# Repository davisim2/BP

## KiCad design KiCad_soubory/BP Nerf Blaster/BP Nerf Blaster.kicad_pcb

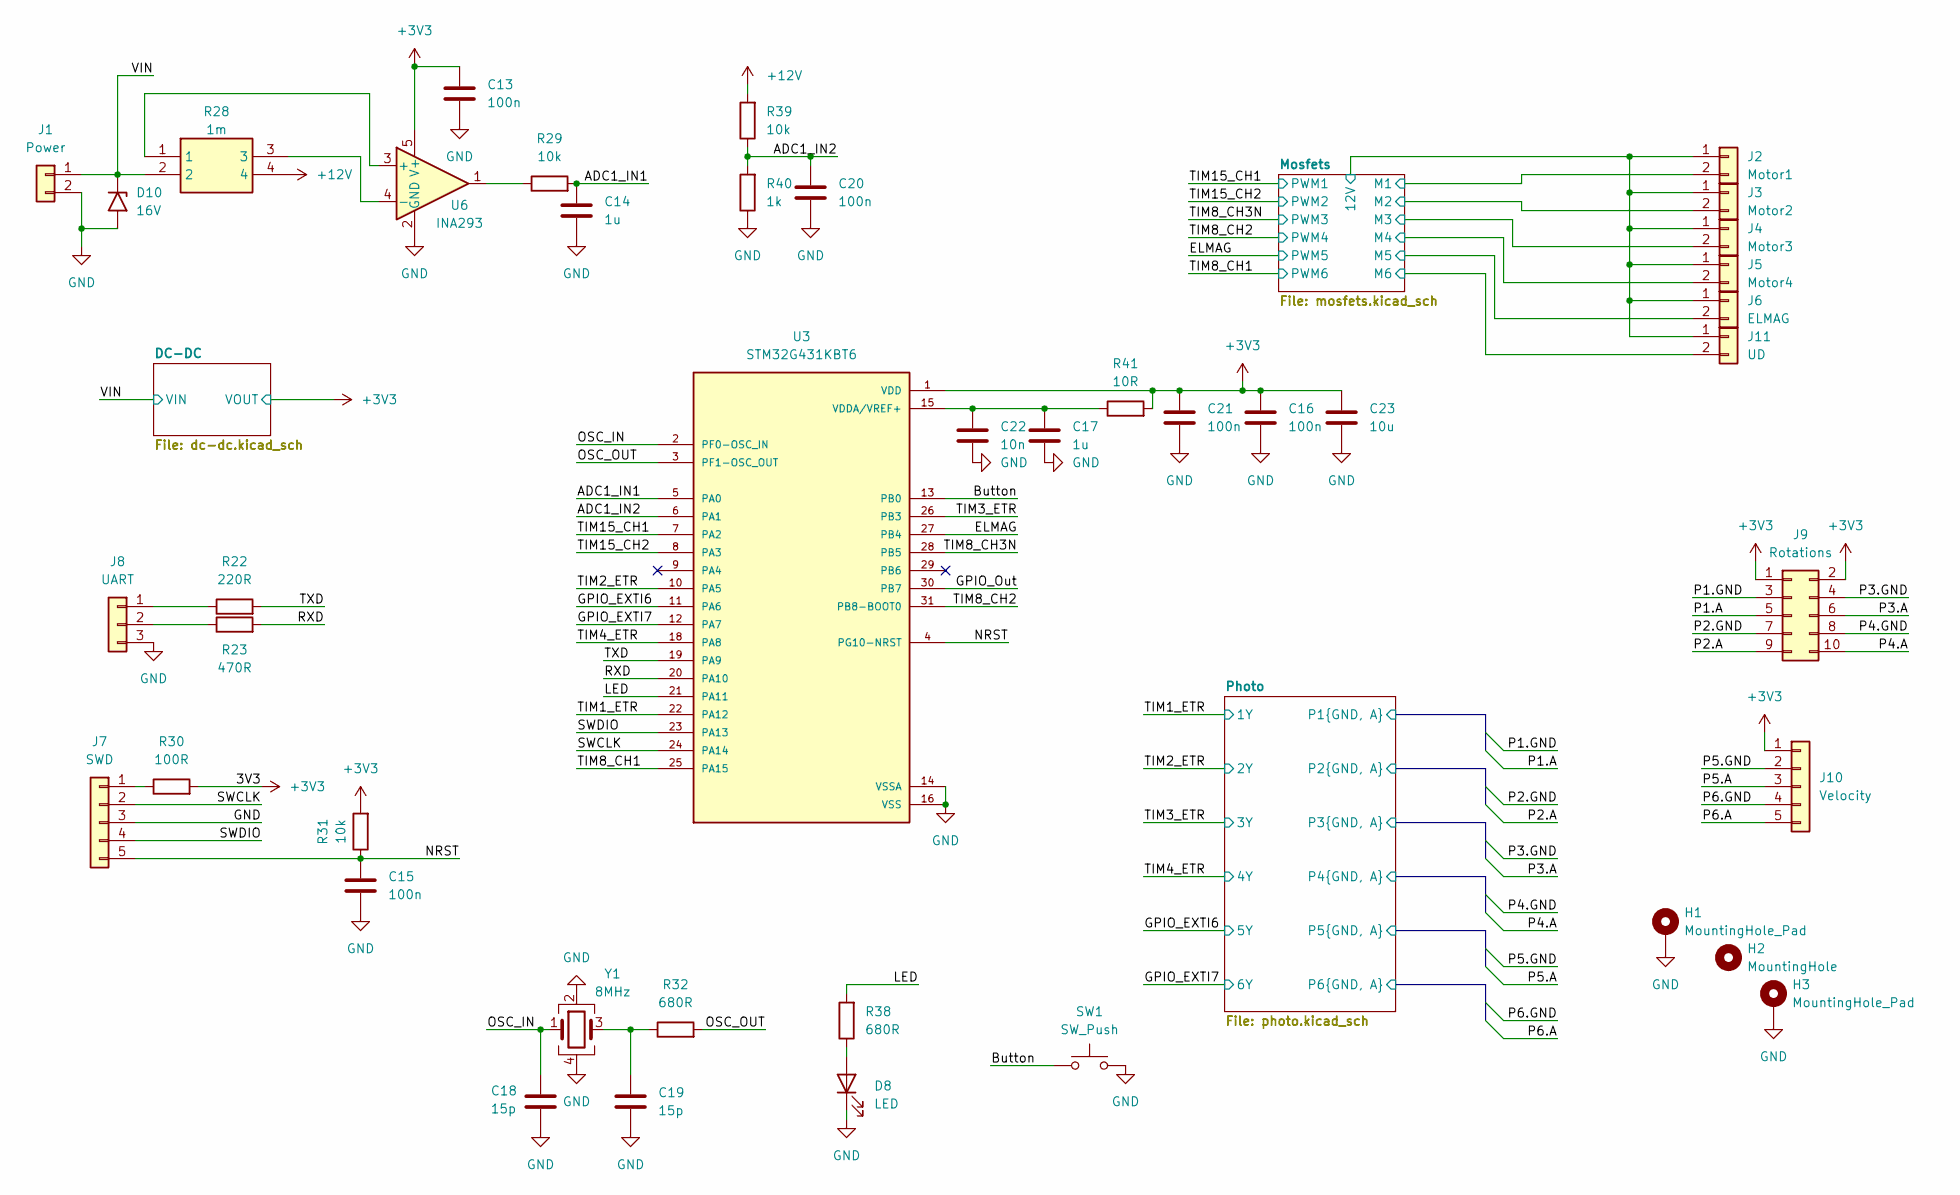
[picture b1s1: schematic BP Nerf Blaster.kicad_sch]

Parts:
C13, C15, C16, C20, C21: 100n; C_0805_2012Metric
C14, C17: 1u; C_0805_2012Metric
C18, C19: 15p; C_0805_2012Metric
C22: 10n; C_0603_1608Metric_Pad1.08x0.95mm_HandSolder
C23: 10u; C_0805_2012Metric
D8: LED; LED_D3.0mm
D10: 16V; D_SMB
H1, H3: MountingHole_Pad; MountingHole_3.2mm_M3_DIN965_Pad
H2: MountingHole; Hole
J1: Power; XT30-f
J2: Motor1; XT30-f
J3: Motor2; XT30-f
J4: Motor3; XT30-f
J5: Motor4; XT30-f
J6: ELMAG; XT30-f
J7: SWD; PinHeader_1x05_P1.27mm_Vertical
J8: UART; PinHeader_1x03_P2.54mm_Vertical
J9: Rotations; PinHeader_2x05_P2.54mm_Vertical
J10: Velocity; PinHeader_1x05_P2.54mm_Vertical
J11: UD; XT30-f
R22: 220R; R_0805_2012Metric
R23: 470R; R_0805_2012Metric
R28: 1m; WSK25121L000FEA; Mouser Part Number 71-WSK25121L000FEA
R29, R31, R39: 10k; R_0805_2012Metric
R30: 100R; R_0805_2012Metric
R32, R38: 680R; R_0805_2012Metric
R40: 1k; R_0805_2012Metric
R41: 10R; R_0805_2012Metric
SW1: SW_Push; SW_PUSH_6mm_H9.5mm
U3: STM32G431KBT6; QFP80P900X900X160-32N; PARTREV 2
U6: INA293; SOT-23-5
Y1: 8MHz; Crystal_SMD_SeikoEpson_FA238-4Pin_3.2x2.5mm

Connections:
+3V3: C13.1, C16.1, C21.1, C23.1, J9.1, J9.2, J10.1, R30.2, R31.2, R41.2, U3.1 (VDD), U3.17 (VDD), U6.5 (V+); also elsewhere on the board
+12V: J2.1, J3.1, J4.1, J5.1, J6.1, J11.1, R28.4, R39.2; also elsewhere on the board
/ADC1_IN1: C14.1, R29.2, U3.5 (PA0)
/ADC1_IN2: C20.1, R39.1, R40.2, U3.6 (PA1)
/Button: SW1.1, U3.13 (PB0)
/ELMAG: U3.27 (PB4); also elsewhere on the board
/GPIO_EXTI6: U3.11 (PA6); also elsewhere on the board
/GPIO_EXTI7: U3.12 (PA7); also elsewhere on the board
/GPIO_Out: U3.30 (PB7)
/LED: R38.2, U3.21 (PA11)
/Mosfets/M1: J2.2; also elsewhere on the board
/Mosfets/M2: J3.2; also elsewhere on the board
/Mosfets/M3: J4.2; also elsewhere on the board
/Mosfets/M4: J5.2; also elsewhere on the board
/Mosfets/M5: J6.2; also elsewhere on the board
/Mosfets/M6: J11.2; also elsewhere on the board
/NRST: C15.1, J7.5, R31.1, U3.4 (PG10-NRST)
/OSC_IN: C18.1, U3.2 (PF0-OSC_IN), Y1.1
/OSC_OUT: R32.2, U3.3 (PF1-OSC_OUT)
/Photo/P1.A: J9.5; also elsewhere on the board
/Photo/P1.GND: J9.3; also elsewhere on the board
/Photo/P2.A: J9.9; also elsewhere on the board
/Photo/P2.GND: J9.7; also elsewhere on the board
/Photo/P3.A: J9.6; also elsewhere on the board
/Photo/P3.GND: J9.4; also elsewhere on the board
/Photo/P4.A: J9.10; also elsewhere on the board
/Photo/P4.GND: J9.8; also elsewhere on the board
/Photo/P5.A: J10.3; also elsewhere on the board
/Photo/P5.GND: J10.2; also elsewhere on the board
/Photo/P6.A: J10.5; also elsewhere on the board
/RXD: R23.2, U3.20 (PA10)
/SWCLK: J7.2, U3.24 (PA14)
/SWDIO: J7.4, U3.23 (PA13)
/TIM1_ETR: U3.22 (PA12); also elsewhere on the board
/TIM2_ETR: U3.10 (PA5); also elsewhere on the board
/TIM3_ETR: U3.26 (PB3); also elsewhere on the board
/TIM4_ETR: U3.18 (PA8); also elsewhere on the board
/TIM8_CH1: U3.25 (PA15); also elsewhere on the board
/TIM8_CH2: U3.31 (PB8-BOOT0); also elsewhere on the board
/TIM8_CH3N: U3.28 (PB5); also elsewhere on the board
/TIM15_CH1: U3.7 (PA2); also elsewhere on the board
/TIM15_CH2: U3.8 (PA3); also elsewhere on the board
/TXD: R22.2, U3.19 (PA9)
/VIN: D10.1 (A1), J1.1, R28.2; also elsewhere on the board
unnamed: C19.1, R32.1, Y1.3
unnamed: D8.2 (A), R38.1
unnamed: J7.1, R30.1
unnamed: J8.1, R22.1
unnamed: J8.2, R23.1
unnamed: R29.1, U6.1
unnamed: C17.1, C22.1, R41.1, U3.15 (VDDA/VREF+)
unnamed: R28.1, U6.3 (+)
unnamed: R28.3, U6.4 (-)

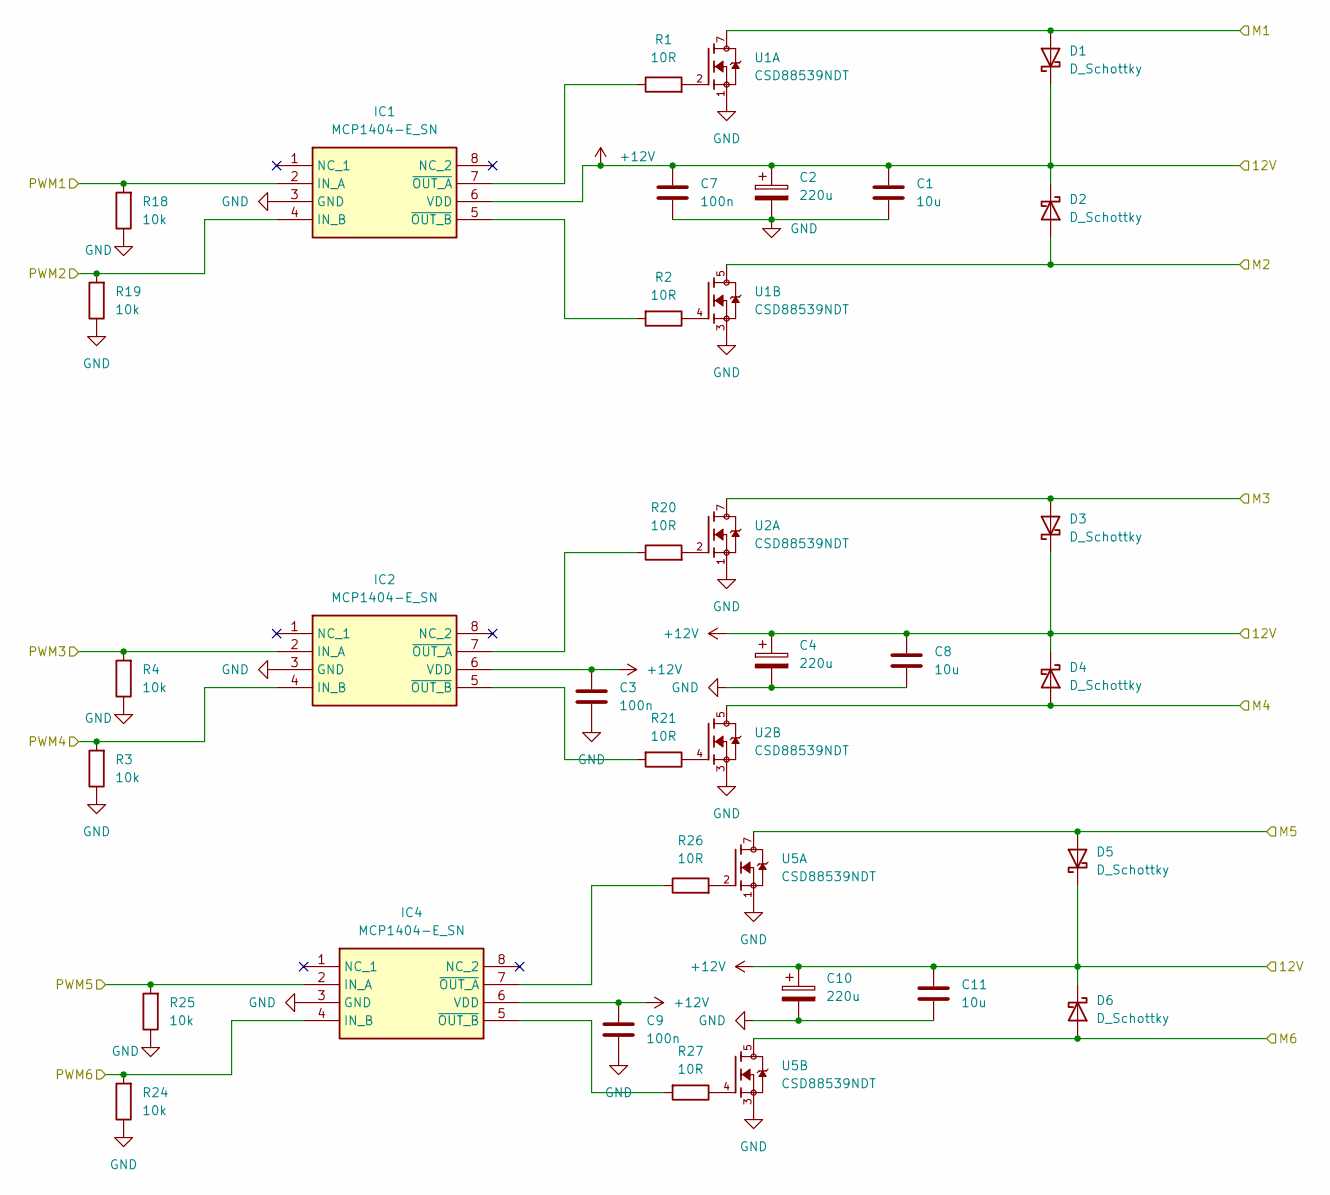
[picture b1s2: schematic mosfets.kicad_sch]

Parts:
C1, C8, C11: 10u; C_1206_3216Metric
C2, C4: 220u; C_Elec_8x10.2
C3, C7, C9: 100n; C_0805_2012Metric
C10: 220u; C_Elec_8x10.2; Mouser 80-EEV227M025A9MAA
D1: D_Schottky; D_SMA; Mouser 625-SSA34-E3
D2, D3, D4, D5, D6: D_Schottky; D_SMA
IC1, IC2, IC4: MCP1404-E_SN; SOIC127P600X175-8N; Mouser Part Number 579-MCP1404-E/SN
R1, R2, R20, R21, R26, R27: 10R; R_0805_2012Metric
R3, R4, R18, R19, R24, R25: 10k; R_0805_2012Metric
U1, U2, U5: CSD88539NDT; SOIC127P600X175-8N; PARTREV February 2014

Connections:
+12V: C1.1, C2.1, C3.1, C4.1, C7.1, C8.1, C9.1, C10.1, C11.1, D1.1 (K), D2.1 (K), D3.1 (K), D4.1 (K), D5.1 (K), D6.1 (K), IC1.6 (VDD), IC2.6 (VDD), IC4.6 (VDD); also elsewhere on the board
/ELMAG: IC4.2 (IN_A), R25.2; also elsewhere on the board
/Mosfets/M1: D1.2 (A), U1.7, U1.8; also elsewhere on the board
/Mosfets/M2: D2.2 (A), U1.5, U1.6; also elsewhere on the board
/Mosfets/M3: D3.2 (A), U2.7, U2.8; also elsewhere on the board
/Mosfets/M4: D4.2 (A), U2.5, U2.6; also elsewhere on the board
/Mosfets/M5: D5.2 (A), U5.7, U5.8; also elsewhere on the board
/Mosfets/M6: D6.2 (A), U5.5, U5.6; also elsewhere on the board
/TIM8_CH1: IC4.4 (IN_B), R24.2; also elsewhere on the board
/TIM8_CH2: IC2.4 (IN_B), R3.2; also elsewhere on the board
/TIM8_CH3N: IC2.2 (IN_A), R4.2; also elsewhere on the board
/TIM15_CH1: IC1.2 (IN_A), R18.2; also elsewhere on the board
/TIM15_CH2: IC1.4 (IN_B), R19.2; also elsewhere on the board
unnamed: IC1.7 (~OUT_A), R1.1
unnamed: IC1.5 (~OUT_B), R2.2
unnamed: IC2.7 (~OUT_A), R20.1
unnamed: IC2.5 (~OUT_B), R21.2
unnamed: IC4.7 (~OUT_A), R26.1
unnamed: IC4.5 (~OUT_B), R27.2
unnamed: R1.2, U1.2
unnamed: R2.1, U1.4
unnamed: R20.2, U2.2
unnamed: R21.1, U2.4
unnamed: R26.2, U5.2
unnamed: R27.1, U5.4

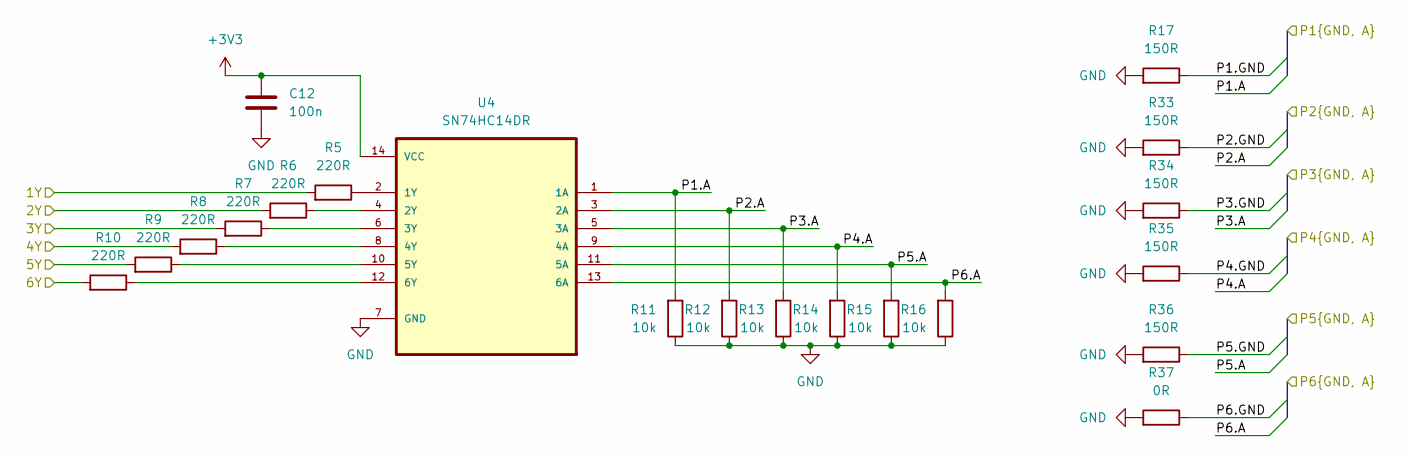
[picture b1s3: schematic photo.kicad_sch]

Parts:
C12: 100n; C_0805_2012Metric
R5, R6, R7, R8, R9, R10: 220R; R_0805_2012Metric
R11, R12, R13, R14, R15, R16: 10k; R_0805_2012Metric
R17, R33, R34, R35, R36: 150R; R_0805_2012Metric
R37: 0R; R_0805_2012Metric
U4: SN74HC14DR; SOIC127P600X175-14N

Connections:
+3V3: C12.1, U4.14 (VCC); also elsewhere on the board
/GPIO_EXTI6: R9.2; also elsewhere on the board
/GPIO_EXTI7: R10.2; also elsewhere on the board
/Photo/P1.A: R11.2, U4.1 (1A); also elsewhere on the board
/Photo/P1.GND: R17.1; also elsewhere on the board
/Photo/P2.A: R12.2, U4.3 (2A); also elsewhere on the board
/Photo/P2.GND: R33.1; also elsewhere on the board
/Photo/P3.A: R13.2, U4.5 (3A); also elsewhere on the board
/Photo/P3.GND: R34.1; also elsewhere on the board
/Photo/P4.A: R14.2, U4.9 (4A); also elsewhere on the board
/Photo/P4.GND: R35.1; also elsewhere on the board
/Photo/P5.A: R15.2, U4.11 (5A); also elsewhere on the board
/Photo/P5.GND: R36.1; also elsewhere on the board
/Photo/P6.A: R16.2, U4.13 (6A); also elsewhere on the board
/Photo/P6.GND: R37.1
/TIM1_ETR: R5.2; also elsewhere on the board
/TIM2_ETR: R6.2; also elsewhere on the board
/TIM3_ETR: R7.2; also elsewhere on the board
/TIM4_ETR: R8.2; also elsewhere on the board
unnamed: R5.1, U4.2 (1Y)
unnamed: R6.1, U4.4 (2Y)
unnamed: R7.1, U4.6 (3Y)
unnamed: R8.1, U4.8 (4Y)
unnamed: R9.1, U4.10 (5Y)
unnamed: R10.1, U4.12 (6Y)

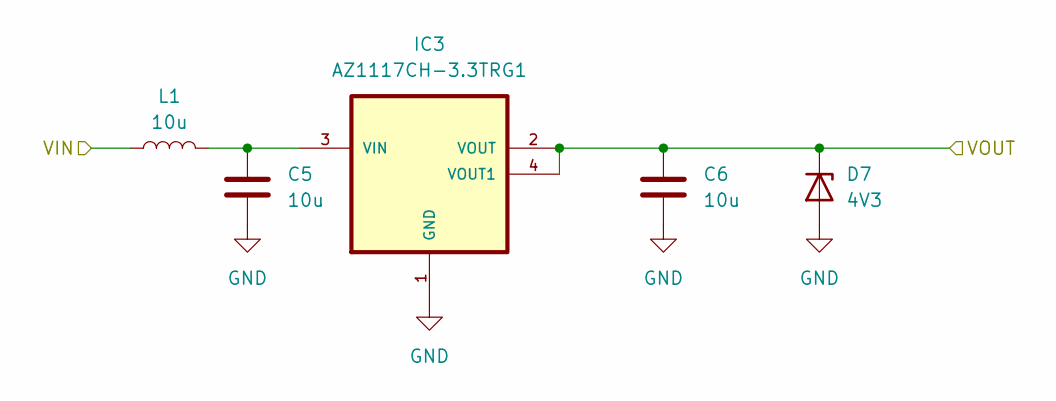
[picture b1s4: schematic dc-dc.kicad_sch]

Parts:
C5, C6: 10u; C_1206_3216Metric
D7: 4V3; D_SMA
IC3: AZ1117CH-3.3TRG1; SOT223
L1: 10u; L_0805_2012Metric

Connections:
+3V3: C6.1, D7.1 (K), IC3.2 (VOUT), IC3.4 (VOUT1); also elsewhere on the board
/VIN: L1.1; also elsewhere on the board
unnamed: C5.1, IC3.3 (VIN), L1.2

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
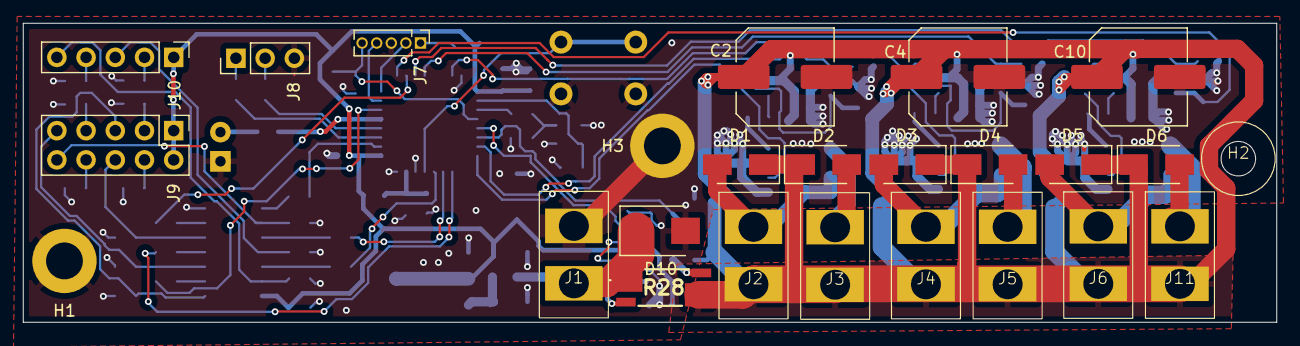
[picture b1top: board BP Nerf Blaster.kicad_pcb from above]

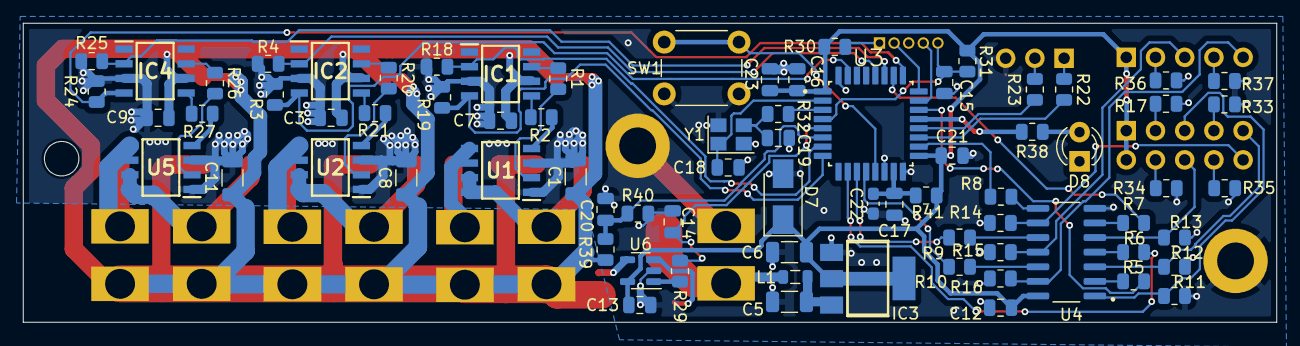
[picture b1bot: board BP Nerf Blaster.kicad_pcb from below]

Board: 2 copper layers, 109.0 x 26.0 mm, 100 parts (75 on the bottom side), 72 nets.

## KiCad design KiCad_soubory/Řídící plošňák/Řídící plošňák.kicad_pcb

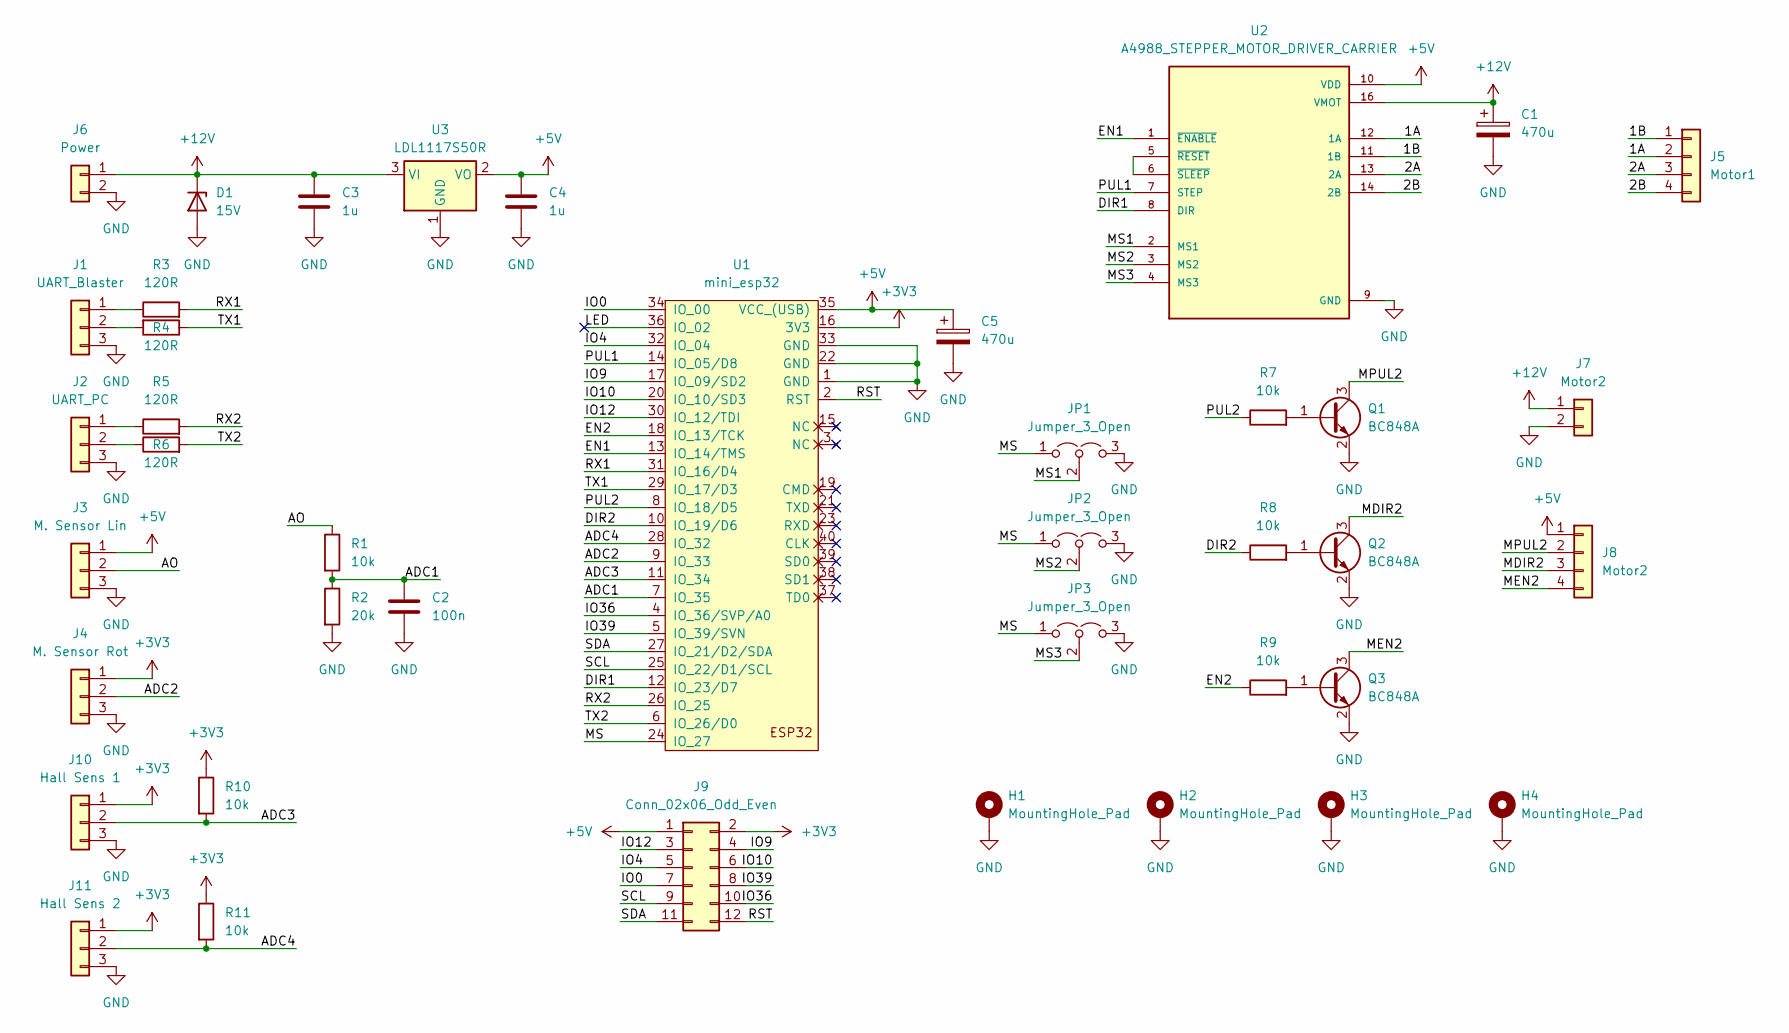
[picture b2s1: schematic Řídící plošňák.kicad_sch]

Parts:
C1, C5: 470u; CP_Elec_8x10
C2: 100n; C_1206_3216Metric_Pad1.33x1.80mm_HandSolder
C3, C4: 1u; C_1206_3216Metric_Pad1.33x1.80mm_HandSolder
D1: 15V; D_SMB_Handsoldering
H1, H2, H3, H4: MountingHole_Pad; MountingHole_4.3mm_M4_DIN965_Pad
J1: UART_Blaster; PinHeader_1x03_P2.54mm_Vertical
J2: UART_PC; PinHeader_1x03_P2.54mm_Vertical
J3: M. Sensor Lin; PinHeader_1x03_P2.54mm_Vertical
J4: M. Sensor Rot; PinHeader_1x03_P2.54mm_Vertical
J5: Motor1; TE_282822-4
J6: Power; XT30-f
J7: Motor2; XT30-f
J8: Motor2; PinHeader_1x04_P2.54mm_Vertical
J9: Conn_02x06_Odd_Even; PinHeader_2x06_P2.54mm_Vertical
J10: Hall Sens 1; PinHeader_1x03_P2.54mm_Vertical
J11: Hall Sens 2; PinHeader_1x03_P2.54mm_Vertical
JP1, JP2, JP3: Jumper_3_Open; SolderJumper-3_P1.3mm_Open_Pad1.0x1.5mm_NumberLabels
Q1, Q2, Q3: BC848A; SOT-23_Handsoldering
R1, R7, R8, R9, R10, R11: 10k; R_1206_3216Metric_Pad1.30x1.75mm_HandSolder
R2: 20k; R_1206_3216Metric_Pad1.30x1.75mm_HandSolder
R3, R4, R5, R6: 120R; R_1206_3216Metric_Pad1.30x1.75mm_HandSolder
U1: mini_esp32; ESP32_mini
U2: A4988_STEPPER_MOTOR_DRIVER_CARRIER; MODULE_A4988_STEPPER_MOTOR_DRIVER_CARRIER
U3: LDL1117S50R; SOT-223-3_TabPin2

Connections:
+3V3: J4.1, J9.2, J10.1, J11.1, R10.1, R11.1, U1.16 (3V3)
+5V: C4.1, C5.1, J3.1, J8.1, J9.1, U1.35 (VCC_(USB)), U2.10 (VDD), U3.2 (VO)
+12V: C1.1, C3.1, D1.1 (K), J6.1, J7.1, U2.16 (VMOT), U3.3 (VI)
/1A: J5.2, U2.12 (1A)
/1B: J5.1, U2.11 (1B)
/2A: J5.3, U2.13 (2A)
/2B: J5.4, U2.14 (2B)
/ADC1: C2.1, R1.2, R2.1, U1.7 (IO_35)
/ADC2: J4.2, U1.9 (IO_33)
/ADC3: J10.2, R10.2, U1.11 (IO_34)
/ADC4: J11.2, R11.2, U1.28 (IO_32)
/AO: J3.2, R1.1
/DIR1: U1.12 (IO_23/D7), U2.8 (DIR)
/DIR2: R8.1, U1.10 (IO_19/D6)
/EN1: U1.13 (IO_14/TMS), U2.1 (~ENABLE)
/EN2: R9.1, U1.18 (IO_13/TCK)
/IO0: J9.7, U1.34 (IO_00)
/IO4: J9.5, U1.32 (IO_04)
/IO9: J9.4, U1.17 (IO_09/SD2)
/IO10: J9.6, U1.20 (IO_10/SD3)
/IO12: J9.3, U1.30 (IO_12/TDI)
/IO36: J9.10, U1.4 (IO_36/SVP/A0)
/IO39: J9.8, U1.5 (IO_39/SVN)
/LED: U1.36 (IO_02)
/MDIR2: J8.3, Q2.3 (C)
/MEN2: J8.4, Q3.3 (C)
/MPUL2: J8.2, Q1.3 (C)
/MS: JP1.1 (A), JP2.1 (A), JP3.1 (A), U1.24 (IO_27)
/MS1: JP1.2 (C), U2.2 (MS1)
/MS2: JP2.2 (C), U2.3 (MS2)
/MS3: JP3.2 (C), U2.4 (MS3)
/PUL1: U1.14 (IO_05/D8), U2.7 (STEP)
/PUL2: R7.1, U1.8 (IO_18/D5)
/RST: J9.12, U1.2 (RST)
/RX1: R3.2, U1.31 (IO_16/D4)
/RX2: R5.2, U1.26 (IO_25)
/SCL: J9.9, U1.25 (IO_22/D1/SCL)
/SDA: J9.11, U1.27 (IO_21/D2/SDA)
/TX1: R4.1, U1.29 (IO_17/D3)
/TX2: R6.2, U1.6 (IO_26/D0)
GND: C1.2, C2.2, C3.2, C4.2, C5.2, D1.2 (A), H1.1, H2.1, H3.1, H4.1, J1.3, J2.3, J3.3, J4.3, J6.2, J7.2, J10.3, J11.3, JP1.3 (B), JP2.3 (B), JP3.3 (B), Q1.2 (E), Q2.2 (E), Q3.2 (E), R2.2, U1.1 (GND), U1.22 (GND), U1.33 (GND), U2.9 (GND), U2.15 (GND), U3.1 (GND)
unnamed: J1.1, R3.1
unnamed: J1.2, R4.2
unnamed: J2.1, R5.1
unnamed: J2.2, R6.1
unnamed: Q1.1 (B), R7.2
unnamed: Q2.1 (B), R8.2
unnamed: Q3.1 (B), R9.2
unnamed: U2.5 (~RESET), U2.6 (~SLEEP)

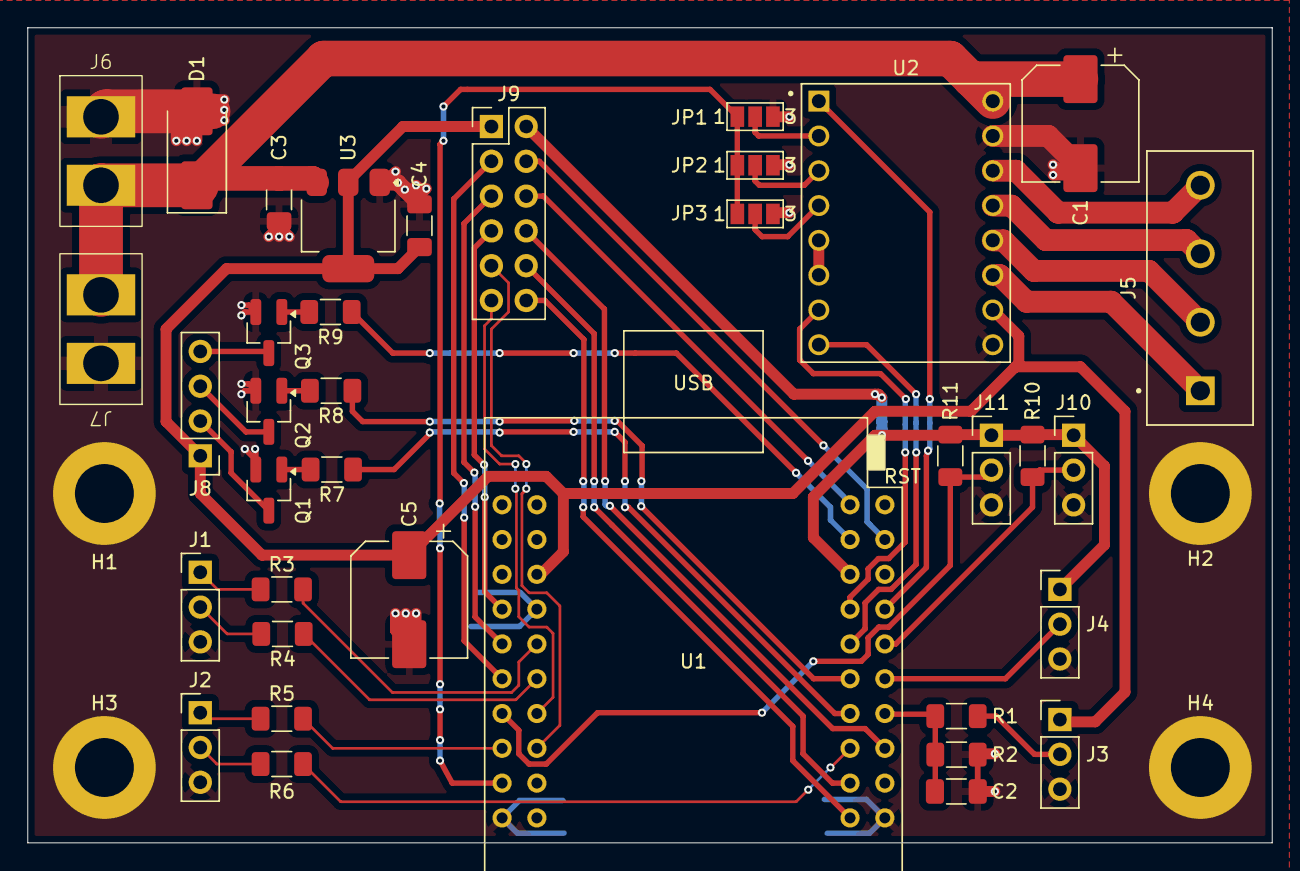
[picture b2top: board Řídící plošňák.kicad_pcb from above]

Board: 2 copper layers, 90.8 x 59.5 mm, 41 parts (0 on the bottom side), 48 nets.

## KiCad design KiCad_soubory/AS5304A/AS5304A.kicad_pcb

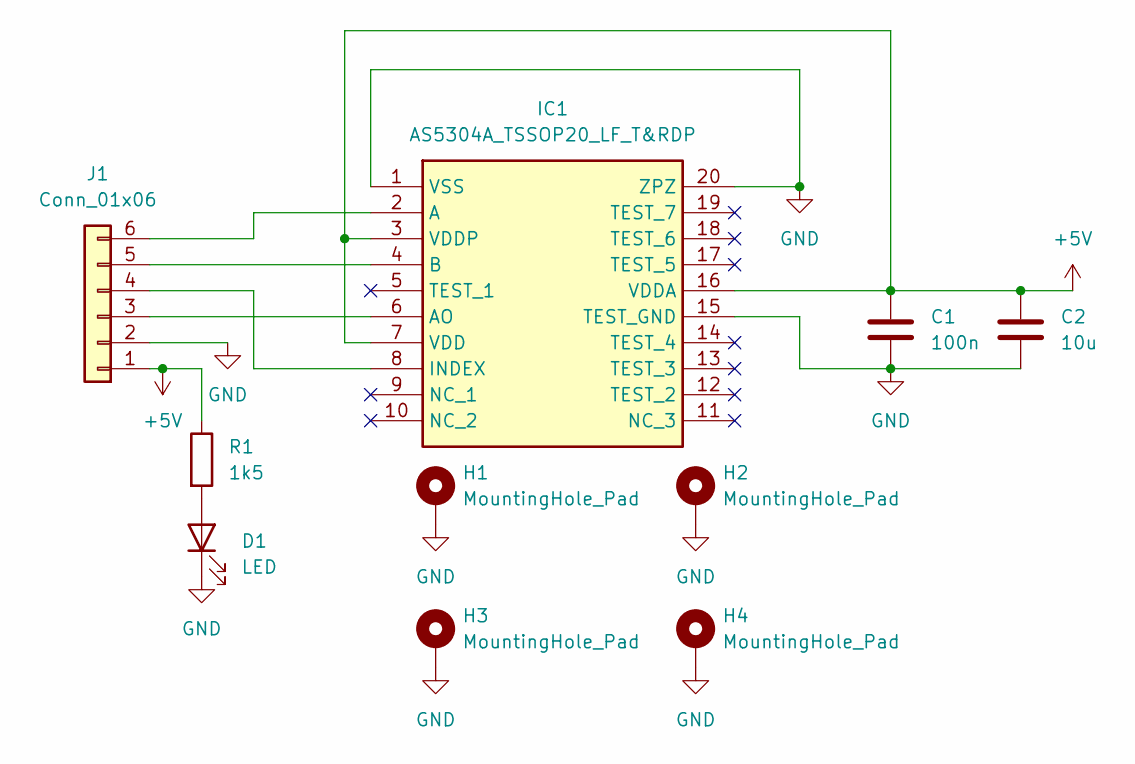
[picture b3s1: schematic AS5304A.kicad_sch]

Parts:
C1: 100n; C_0805_2012Metric_Pad1.18x1.45mm_HandSolder
C2: 10u; C_1206_3216Metric_Pad1.33x1.80mm_HandSolder
D1: LED; LED_1206_3216Metric_Pad1.42x1.75mm_HandSolder
H1, H2, H3, H4: MountingHole_Pad; MountingHole_3.2mm_M3_DIN965_Pad
IC1: AS5304A_TSSOP20_LF_T&RDP; SOP65P640X120-20N; Mouser Part Number 985-AS5304A-ATSM
J1: Conn_01x06; PinHeader_1x06_P2.54mm_Vertical
R1: 1k5; R_1206_3216Metric_Pad1.30x1.75mm_HandSolder

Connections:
+5V: C1.1, C2.1, IC1.3 (VDDP), IC1.7 (VDD), IC1.16 (VDDA), J1.1, R1.1
GND: C1.2, C2.2, D1.1 (K), H1.1, H2.1, H3.1, H4.1, IC1.1 (VSS), IC1.15 (TEST_GND), IC1.20 (ZPZ), J1.2
unnamed: D1.2 (A), R1.2
unnamed: IC1.2 (A), J1.6
unnamed: IC1.6 (AO), J1.3
unnamed: IC1.4 (B), J1.5
unnamed: IC1.8 (INDEX), J1.4

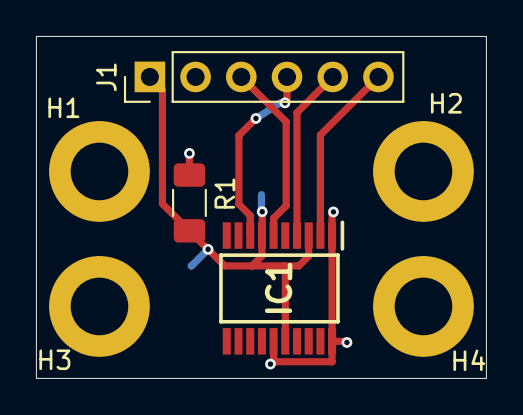
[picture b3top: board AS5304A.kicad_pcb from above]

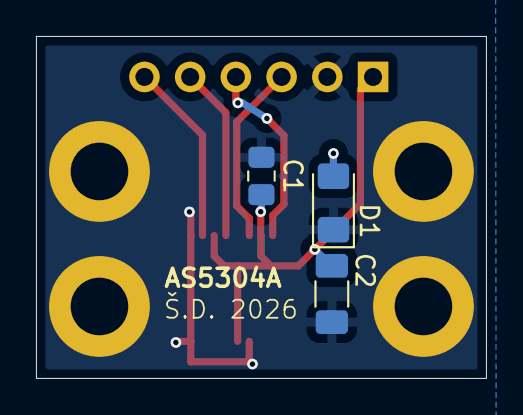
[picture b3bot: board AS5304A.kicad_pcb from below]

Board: 2 copper layers, 25.0 x 19.0 mm, 10 parts (3 on the bottom side), 7 nets.

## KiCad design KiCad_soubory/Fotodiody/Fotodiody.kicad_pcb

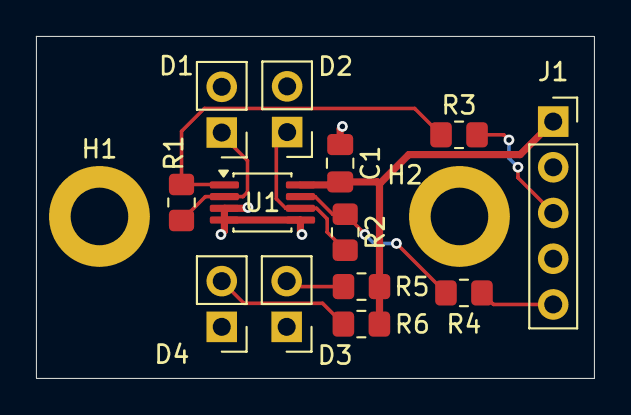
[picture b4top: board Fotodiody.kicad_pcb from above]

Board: 2 copper layers, 31.0 x 19.0 mm, 15 parts (0 on the bottom side), 10 nets.

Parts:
C1: 100n; C_0805_2012Metric_Pad1.18x1.45mm_HandSolder
D1, D2: PD204; PinHeader_1x02_P2.54mm_Vertical
D3, D4: LED; PinHeader_1x02_P2.54mm_Vertical
H1, H2: MountingHole_Pad; MountingHole_3.2mm_M3_DIN965_Pad
J1: Conn_01x05; PinSocket_1x05_P2.54mm_Vertical
R1, R2: 470k; R_0805_2012Metric_Pad1.20x1.40mm_HandSolder
R3, R4: 120R; R_0805_2012Metric_Pad1.20x1.40mm_HandSolder
R5, R6: 130; R_0805_2012Metric_Pad1.20x1.40mm_HandSolder
U1: MCP6002-xMS; MSOP-8_3x3mm_P0.65mm

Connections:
+3V3: C1.2, J1.1, R5.2, R6.2, U1.8 (V+)
/P5A: J1.3, R3.2
/P6A: J1.5, R4.2
GND: C1.1, D1.2 (K), D2.2 (K), D3.1 (K), D4.1 (K), H1.1, H2.1, J1.2, J1.4, U1.3 (+), U1.4 (V-), U1.5 (+)
unnamed: D1.1 (A), R1.1, U1.2 (-)
unnamed: D2.1 (A), R2.1, U1.6 (-)
unnamed: D3.2 (A), R5.1
unnamed: D4.2 (A), R6.1
unnamed: R1.2, R3.1, U1.1
unnamed: R2.2, R4.1, U1.7

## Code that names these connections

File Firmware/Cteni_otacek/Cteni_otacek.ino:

// ===== UART1 na PA10 (RX) a PA9 (TX) =====
HardwareSerial MySerial(PA10, PA9);

// ===== PWM piny =====
const int pwmPin1 = PB5;    // TIM8_CH3N
const int pwmPin2 = PA3;    // TIM15_CH2
const int pwmPin3 = PA2;    // TIM15_CH1
const int pwmPin4 = PB8;    // TIM8_CH2

// ===== Ostatní piny =====
const int ledPin    = PA11;
const int magnetPin = PA15; // TIM8_CH1

// ===== Senzory QRD1114 (TIM_ETR) =====
const int sens1Pin = PA12;  // TIM1_ETR
const int sens2Pin = PA5;   // TIM2_ETR
const int sens3Pin = PB3;   // TIM3_ETR
const int sens4Pin = PA8;   // TIM4_ETR

// ===== Proměnné pro počítání pulzů (volatile pro přístup z ISR) =====
volatile uint32_t pulseCount1 = 0;
volatile uint32_t pulseCount2 = 0;
volatile uint32_t pulseCount3 = 0;
volatile uint32_t pulseCount4 = 0;

// ===== Proměnné pro výpočet RPM =====
uint32_t lastRpmTime = 0;
const uint32_t rpmInterval = 250; // Interval výpočtu v ms (250 ms = 4x za vteřinu)

uint32_t lastPulseCount1 = 0;
uint32_t lastPulseCount2 = 0;
uint32_t lastPulseCount3 = 0;
uint32_t lastPulseCount4 = 0;

uint32_t currentRpm1 = 0;
uint32_t currentRpm2 = 0;
uint32_t currentRpm3 = 0;
uint32_t currentRpm4 = 0;

// ===== Úrovně výkonu =====
uint8_t quarter       = 64;   //  25 %
uint8_t half          = 128;  //  50 %
uint8_t threeQuarters = 192;  //  75 %
uint8_t full          = 250;  // ~100 %

bool ledState    = true;
bool magnetState = false;

// ===== Obslužné rutiny přerušení (ISR) =====
void isr1() { pulseCount1++; }
void isr2() { pulseCount2++; }
void isr3() { pulseCount3++; }
void isr4() { pulseCount4++; }

void setup() {
  const uint32_t freq = 1000;  // 1 kHz PWM

  pinMode(pwmPin1, OUTPUT);
  pinMode(pwmPin2, OUTPUT);
  pinMode(pwmPin3, OUTPUT);
  pinMode(pwmPin4, OUTPUT);

  pinMode(ledPin, OUTPUT);
  pinMode(magnetPin, OUTPUT);

  // Nastavení vstupů pro senzory
  // Máte zapojený 10k rezistor na zem, takže RISING hrana znamená detekci odrazu
  pinMode(sens1Pin, INPUT);
  pinMode(sens2Pin, INPUT);
  pinMode(sens3Pin, INPUT);
  pinMode(sens4Pin, INPUT);

  // Připojení přerušení
  attachInterrupt(digitalPinToInterrupt(sens1Pin), isr1, RISING);
  attachInterrupt(digitalPinToInterrupt(sens2Pin), isr2, RISING);
  attachInterrupt(digitalPinToInterrupt(sens3Pin), isr3, RISING);
  attachInterrupt(digitalPinToInterrupt(sens4Pin), isr4, RISING);

  analogWriteResolution(8);
  analogWriteFrequency(freq);

  // Vše vypnuto
  analogWrite(pwmPin1, 0);
  analogWrite(pwmPin2, 0);
  analogWrite(pwmPin3, 0);
  analogWrite(pwmPin4, 0);

  digitalWrite(ledPin, HIGH);
  digitalWrite(magnetPin, LOW);

  MySerial.begin(115200);
  delay(500);
  
  MySerial.println("STM32 Ready (RPM Mereni)");
  MySerial.println("Ovladani: 1,2,3,4 (1/2 vykonu jednotlivce)");
  MySerial.println("Hromadne: z (1/4), b (1/2), n (3/4), m (plny)");
  MySerial.println("v : Vypsat RPM");
  MySerial.println("o : Vypnout vse");
}

void loop() {
  uint32_t currentMillis = millis();

  // ===== Periodický výpočet RPM na pozadí =====
  if (currentMillis - lastRpmTime >= rpmInterval) {
    uint32_t dt = currentMillis - lastRpmTime;

    // Dočasné zakázání přerušení pro bezpečné přečtení 32bitových proměnných
    noInterrupts();
    uint32_t pc1 = pulseCount1;
    uint32_t pc2 = pulseCount2;
    uint32_t pc3 = pulseCount3;
    uint32_t pc4 = pulseCount4;
    interrupts(); // Okamžité opětovné povolení

    // Výpočet: (Přírůstek pulzů * 60000 ms) / časový rozdíl
    currentRpm1 = ((pc1 - lastPulseCount1) * 60000UL) / dt;
    currentRpm2 = ((pc2 - lastPulseCount2) * 60000UL) / dt;
    currentRpm3 = ((pc3 - lastPulseCount3) * 60000UL) / dt;
    currentRpm4 = ((pc4 - lastPulseCount4) * 60000UL) / dt;

    // Uložení stavů pro další cyklus
    lastPulseCount1 = pc1;
    lastPulseCount2 = pc2;
    lastPulseCount3 = pc3;
    lastPulseCount4 = pc4;
    lastRpmTime = currentMillis;
  }

  // ===== Zpracování příkazů z UARTu =====
  if (MySerial.available() > 0) {
    char cmd = MySerial.read();

    switch (cmd) {
      // ===== VÝPIS RPM =====
      case 'v':
        MySerial.println("--- Aktualni RPM ---");
        MySerial.print("M1 (PB5):  "); MySerial.println(currentRpm1);
        MySerial.print("M2 (PA3):  "); MySerial.println(currentRpm2);
        MySerial.print("M3 (PA2):  "); MySerial.println(currentRpm3);
        MySerial.print("M4 (PB8):  "); MySerial.println(currentRpm4);
        MySerial.println("--------------------");
        break;

      // ===== INDIVIDUÁLNÍ výkon (1/2) =====
      case '1': analogWrite(pwmPin1, half); break;
      case '2': analogWrite(pwmPin2, half); break;
      case '3': analogWrite(pwmPin3, half); break;
      case '4': analogWrite(pwmPin4, half); break;

      // ===== HROMADNÝ výkon =====
      case 'z': // 1/4
        analogWrite(pwmPin1, quarter); analogWrite(pwmPin2, quarter);
        analogWrite(pwmPin3, quarter); analogWrite(pwmPin4, quarter); 
        break;
        
      case 'b': // 1/2
        analogWrite(pwmPin1, half); analogWrite(pwmPin2, half);
        analogWrite(pwmPin3, half); analogWrite(pwmPin4, half); 
        break;

      case 'n': // 3/4
        analogWrite(pwmPin1, threeQuarters); analogWrite(pwmPin2, threeQuarters);
        analogWrite(pwmPin3, threeQuarters); analogWrite(pwmPin4, threeQuarters); 
        break;

      case 'm': // PLNY
        analogWrite(pwmPin1, full); analogWrite(pwmPin2, full);
        analogWrite(pwmPin3, full); analogWrite(pwmPin4, full); 
        break;

      // ===== LED toggle =====
      case 'l':
        ledState = !ledState;
        digitalWrite(ledPin, ledState);
        break;

      // ===== Elektromagnet toggle =====
      case ' ':
      case 'e':
        magnetState = !magnetState;
        digitalWrite(magnetPin, magnetState);
        delay(500);
        magnetState = !magnetState;
        digitalWrite(magnetPin, magnetState);
        break;

      // ===== Vypnout vše =====
      case 'o':
        analogWrite(pwmPin1, 0);
        analogWrite(pwmPin2, 0);
        analogWrite(pwmPin3, 0);
        analogWrite(pwmPin4, 0);
        digitalWrite(ledPin, LOW);
        digitalWrite(magnetPin, LOW);
        ledState = false;
        magnetState = false;
        break;

      default:
        // Ignoruj prázdné znaky (CR/LF z terminálu)
        if (cmd != '\r' && cmd != '\n' && cmd > 0) {
          MySerial.print("Neznamy prikaz: ");
          MySerial.println(cmd);
        }
        break;
    }
  }
}

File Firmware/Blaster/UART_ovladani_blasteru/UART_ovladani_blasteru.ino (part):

// ===== UART1 na PA10 (RX) a PA9 (TX) =====
HardwareSerial MySerial(PA10, PA9);

// ===== PWM piny a periferie =====
const int pwmPin1   = PB5;  // TIM8_CH3N
const int pwmPin2   = PA3;  // TIM15_CH2
const int pwmPin3   = PA2;  // TIM15_CH1
const int pwmPin4   = PB8;  // TIM8_CH2
const int ledPin    = PA11; // LED dioda
const int laserPin  = PB4;  // Laser
const int magnetPin = PA15; // TIM8_CH1 (Elektromagnet)
const int buttonPin = PB0;  // Fyzické tlačítko

// ===== Analogové piny pro měření =====
const int adcCurrPin = PA0; // ADC1_IN1 (Proud - INA293)
const int adcVoltPin = PA1; // ADC1_IN2 (Napětí - Dělič)

// ===== Piny pro optické závory =====
const int gate1Pin = PA7;  // Závora 1
const int gate2Pin = PA6;  // Závora 2

// ===== Úrovně výkonu a frekvence PWM =====
uint8_t quarter       = 64;   //  25 %
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
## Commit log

2026-05-22 Added Firmware and step file
2026-05-22 Initial commit all files
2026-05-22 Added model
2026-05-22 Added firmware version
2026-05-22 Added better firmware structure
2026-05-22 Barevne znaceni vodicu
